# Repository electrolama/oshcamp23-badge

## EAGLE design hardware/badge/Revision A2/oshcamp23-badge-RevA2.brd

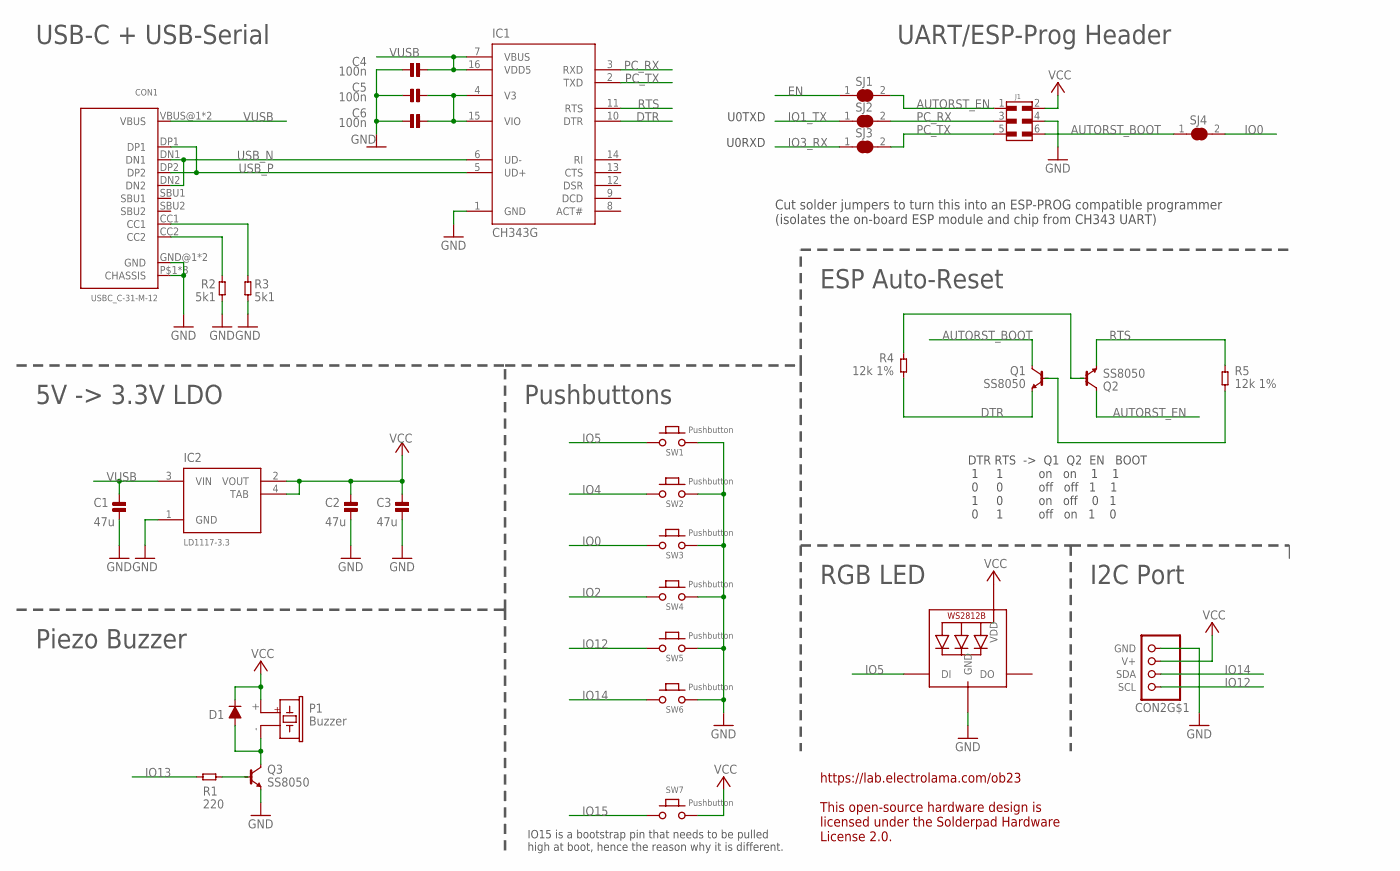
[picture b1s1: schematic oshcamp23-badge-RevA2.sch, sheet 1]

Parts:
C1, C2, C3: 47u; _PKG_C_1206; MPN CL31A476MPHNNNE; JLCASSY C96123
C4, C5, C6: 100n; _PKG_C_0402; JLCASSY C307331
CON1: USBC_C-31-M-12; JLCASSY C165948
CON2: STEMMA_I2C_QT; JST_SH4; JLCASSY C145956
D1: DIODE-SWITCHING-1N4148W; _PKG_SOD123
IC1: CH343G; _PKG_SOP16; JLCASSY C2844153
IC2: LD1117-3.3; _PKG_SOT223-4_TI-DCY4; JLCASSY C6186
J1: 61030621121; JLCASSY C780054
LED1: WS2812B5050; WS2812B
P1: Buzzer; MLT-8530; JLCASSY C94599
Q1, Q2, Q3: SS8050; SOT96P237X111-3N; JLCASSY C2150
R1: 220; _PKG_R_0603; JLCASSY C22962
R2, R3: 5k1; _PKG_R_0603; JLCASSY C23186
R4, R5: 12k 1%; _PKG_R_0402; JLCASSY C25752
SJ1, SJ2, SJ3, SJ4: SJ-SHORT
SW1, SW2, SW3, SW4, SW5, SW6, SW7: Pushbutton; GENERIC_SPNO_4P_6X6MM; JLCASSY C620316

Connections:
AUTORST_BOOT: J1.6, Q1.3 (C), SJ4.1
AUTORST_EN: J1.1, Q2.3 (C), SJ1.2
CH343_3V: C5.1, C6.1, IC1.4 (V3), IC1.15 (VIO)
DTR: IC1.10 (DTR), Q1.2 (E), R4.1
EN: SJ1.1; also elsewhere on the board
GND: C1.2, C2.2, C3.2, C4.2, C5.2, C6.2, CON1.GND@1 (GND), CON1.GND@2 (GND), CON1.P$1 (CHASSIS), CON1.P$2 (CHASSIS), CON1.P$3 (CHASSIS), CON1.P$4 (CHASSIS), CON1.P$5 (CHASSIS), CON1.P$6 (CHASSIS), CON1.P$7 (CHASSIS), CON1.P$8 (CHASSIS), CON2.1 (GND), IC1.1 (GND), IC2.1 (GND), J1.4, LED1.3-GND (GND), Q3.2 (E), R2.1, R3.1, SW1.P$3 (2), SW1.P$4 (2), SW2.P$3 (2), SW2.P$4 (2), SW3.P$3 (2), SW3.P$4 (2), SW4.P$3 (2), SW4.P$4 (2), SW5.P$3 (2), SW5.P$4 (2), SW6.P$3 (2), SW6.P$4 (2); also elsewhere on the board
IO0: SJ4.2, SW3.P$1 (1), SW3.P$2 (1); also elsewhere on the board
IO1_TX: SJ2.1; also elsewhere on the board
IO2: SW4.P$1 (1), SW4.P$2 (1); also elsewhere on the board
IO3_RX: SJ3.1; also elsewhere on the board
IO4: SW2.P$1 (1), SW2.P$2 (1); also elsewhere on the board
IO5: LED1.4-DIN (DI), SW1.P$1 (1), SW1.P$2 (1); also elsewhere on the board
IO12: CON2.4 (SCL), SW5.P$1 (1), SW5.P$2 (1); also elsewhere on the board
IO13: R1.2; also elsewhere on the board
IO14: CON2.3 (SDA), SW6.P$1 (1), SW6.P$2 (1); also elsewhere on the board
IO15: SW7.P$1 (1), SW7.P$2 (1); also elsewhere on the board
unnamed: Q1.1 (B), R5.1
unnamed: D1.2 (A), P1.-, Q3.3 (C)
unnamed: Q2.1 (B), R4.2
unnamed: CON1.CC1, R3.2
unnamed: CON1.CC2, R2.2
unnamed: Q3.1 (B), R1.1
PC_RX: IC1.3 (RXD), J1.3, SJ2.2
PC_TX: IC1.2 (TXD), J1.5, SJ3.2
RTS: IC1.11 (RTS), Q2.2 (E), R5.2
USB_N: CON1.DN1, CON1.DN2, IC1.6 (UD-)
USB_P: CON1.DP1, CON1.DP2, IC1.5 (UD+)
VCC: C2.1, C3.1, CON2.2 (V+), D1.1 (C), IC2.2 (VOUT), IC2.4 (TAB), J1.2, LED1.1-VDD (VDD), P1.+, SW7.P$3 (2), SW7.P$4 (2); also elsewhere on the board
VUSB: C1.1, C4.1, CON1.VBUS@1 (VBUS), CON1.VBUS@2 (VBUS), IC1.7 (VBUS), IC1.16 (VDD5), IC2.3 (VIN)

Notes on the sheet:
DTR RTS -> Q1 Q2 EN BOOT 1 1 on on 1 1 0 0 off off 1 1 1 0 on off 0 1 0 1 off on 1 0
U0TXD
U0RXD
Cut solder jumpers to turn this into an ESP-PROG compatible programmer (isolates the on-board ESP module and chip from CH343 UART)
USB-C + USB-Serial
UART/ESP-Prog Header
ESP Auto-Reset
RGB LED
I2C Port
Pushbuttons
5V -> 3.3V LDO
Piezo Buzzer
https://lab.electrolama.com/ob23 This open-source hardware design is licensed under the Solderpad Hardware License 2.0.
IO15 is a bootstrap pin that needs to be pulled high at boot, hence the reason why it is different.

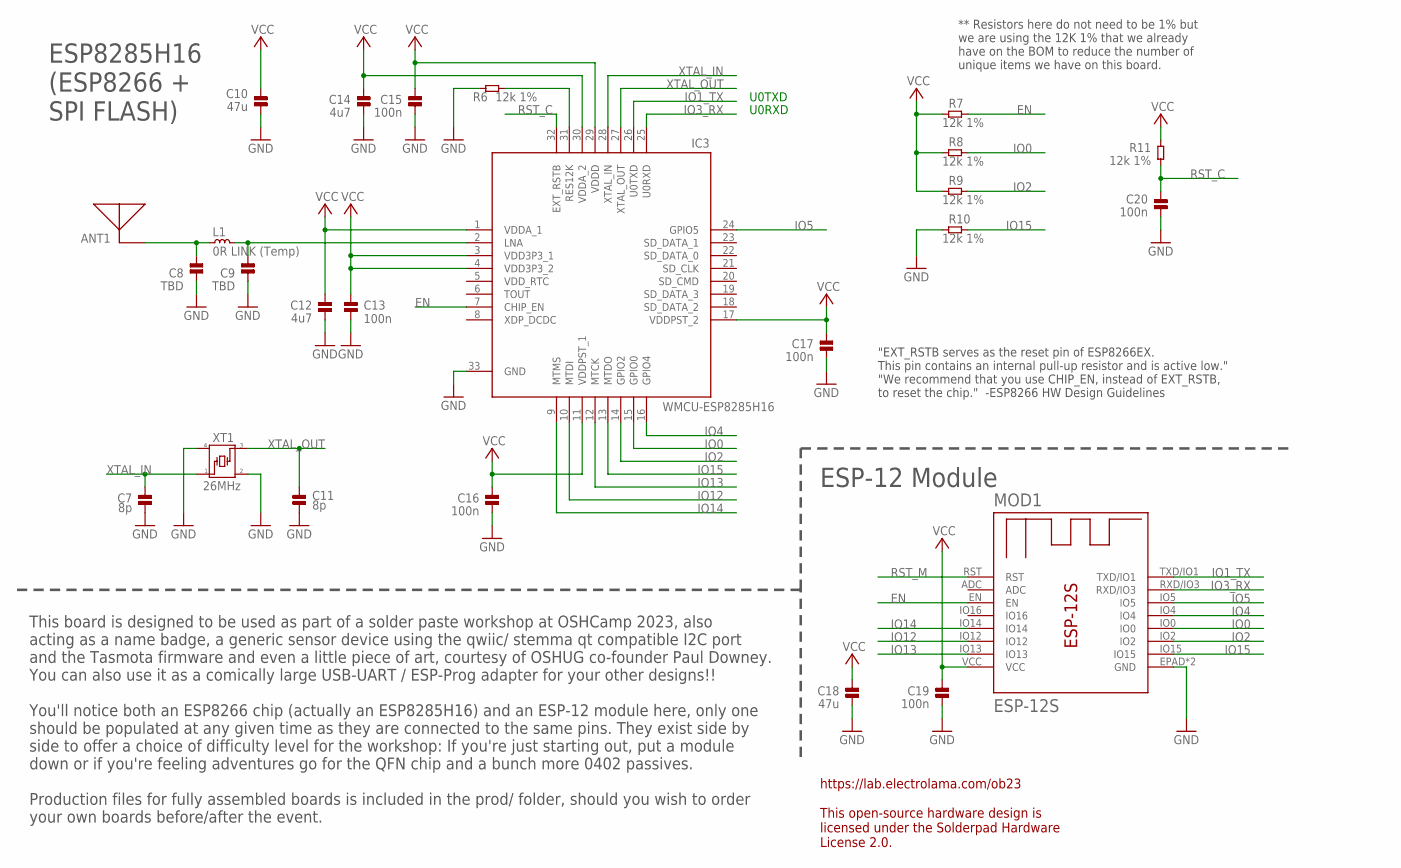
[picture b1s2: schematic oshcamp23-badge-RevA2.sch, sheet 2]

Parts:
ANT1: ANT3216LL00R2400A; YAGEO-ANT3216LL00R2400A; JLCASSY C293767
C7, C11: 8p; _PKG_C_0402; JLCASSY C1578
C8, C9: TBD; _PKG_C_0402_NOTHERMALS
C10, C18: 47u; _PKG_C_1206; MPN CL31A476MPHNNNE; JLCASSY C96123
C12, C14: 4u7; _PKG_C_0402_NOTHERMALS; JLCASSY C23733
C13, C15, C16, C17, C20: 100n; _PKG_C_0402_NOTHERMALS; JLCASSY C307331
C19: 100n; _PKG_C_0402; JLCASSY C307331
IC3: WMCU-ESP8285H16; QFN50P500X500X90-33N; JLCASSY C967019
L1: 0R LINK (Temp); _PKG_L_0402
MOD1: ESP-12S; JLCASSY C82898
R6, R7, R8, R9, R10, R11: 12k 1%; _PKG_R_0402; JLCASSY C25752
XT1: 26MHz; XTAL-4P-2016; JLCASSY C2762193

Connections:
ANT: C9.2, IC3.2 (LNA), L1.2
ANT': ANT1.S1, C8.2, L1.1
EN: IC3.7 (CHIP_EN), MOD1.EN, R7.2; also elsewhere on the board
GND: C7.1, C8.1, C9.1, C10.2, C11.1, C12.1, C13.1, C14.1, C15.1, C16.1, C17.1, C18.2, C19.2, C20.1, IC3.33 (GND), MOD1.EPAD (GND), MOD1.GND, R6.2, R10.1, XT1.2, XT1.4; also elsewhere on the board
IO0: IC3.15 (GPIO0), MOD1.IO0, R8.2; also elsewhere on the board
IO1_TX: IC3.26 (U0TXD), MOD1.TXD/IO1; also elsewhere on the board
IO2: IC3.14 (GPIO2), MOD1.IO2, R9.2; also elsewhere on the board
IO3_RX: IC3.25 (U0RXD), MOD1.RXD/IO3; also elsewhere on the board
IO4: IC3.16 (GPIO4), MOD1.IO4; also elsewhere on the board
IO5: IC3.24 (GPIO5), MOD1.IO5; also elsewhere on the board
IO12: IC3.10 (MTDI), MOD1.IO12; also elsewhere on the board
IO13: IC3.12 (MTCK), MOD1.IO13; also elsewhere on the board
IO14: IC3.9 (MTMS), MOD1.IO14; also elsewhere on the board
IO15: IC3.13 (MTDO), MOD1.IO15, R10.2; also elsewhere on the board
unnamed: IC3.31 (RES12K), R6.1
RST_C: C20.2, IC3.32 (EXT_RSTB), R11.1
RST_M: MOD1.RST
VCC: C10.1, C12.2, C13.2, C14.2, C15.2, C16.2, C17.2, C18.1, C19.1, IC3.1 (VDDA_1), IC3.3 (VDD3P3_1), IC3.4 (VDD3P3_2), IC3.11 (VDDPST_1), IC3.17 (VDDPST_2), IC3.29 (VDDD), IC3.30 (VDDA_2), MOD1.VCC, R7.1, R8.1, R9.1, R11.2; also elsewhere on the board
XTAL_IN: C7.2, IC3.28 (XTAL_IN), XT1.1
XTAL_OUT: C11.2, IC3.27 (XTAL_OUT), XT1.3

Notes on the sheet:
U0TXD
U0RXD
"EXT_RSTB serves as the reset pin of ESP8266EX. This pin contains an internal pull-up resistor and is active low." "We recommend that you use CHIP_EN, instead of EXT_RSTB, to reset the chip." -ESP8266 HW Design Guidelines
This board is designed to be used as part of a solder paste workshop at OSHCamp 2023, also acting as a name badge, a generic sensor device using the qwiic/ stemma qt compatible I2C port and the Tasmota firmware and even a little piece of art, courtesy of OSHUG co-founder Paul Downey. You can also u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
https://lab.electrolama.com/ob23 This open-source hardware design is licensed under the Solderpad Hardware License 2.0.
ESP-12 Module
ESP8285H16 (ESP8266 + SPI FLASH)
ANT1
** Resistors here do not need to be 1% but we are using the 12K 1% that we already have on the BOM to reduce the number of unique items we have on this board.

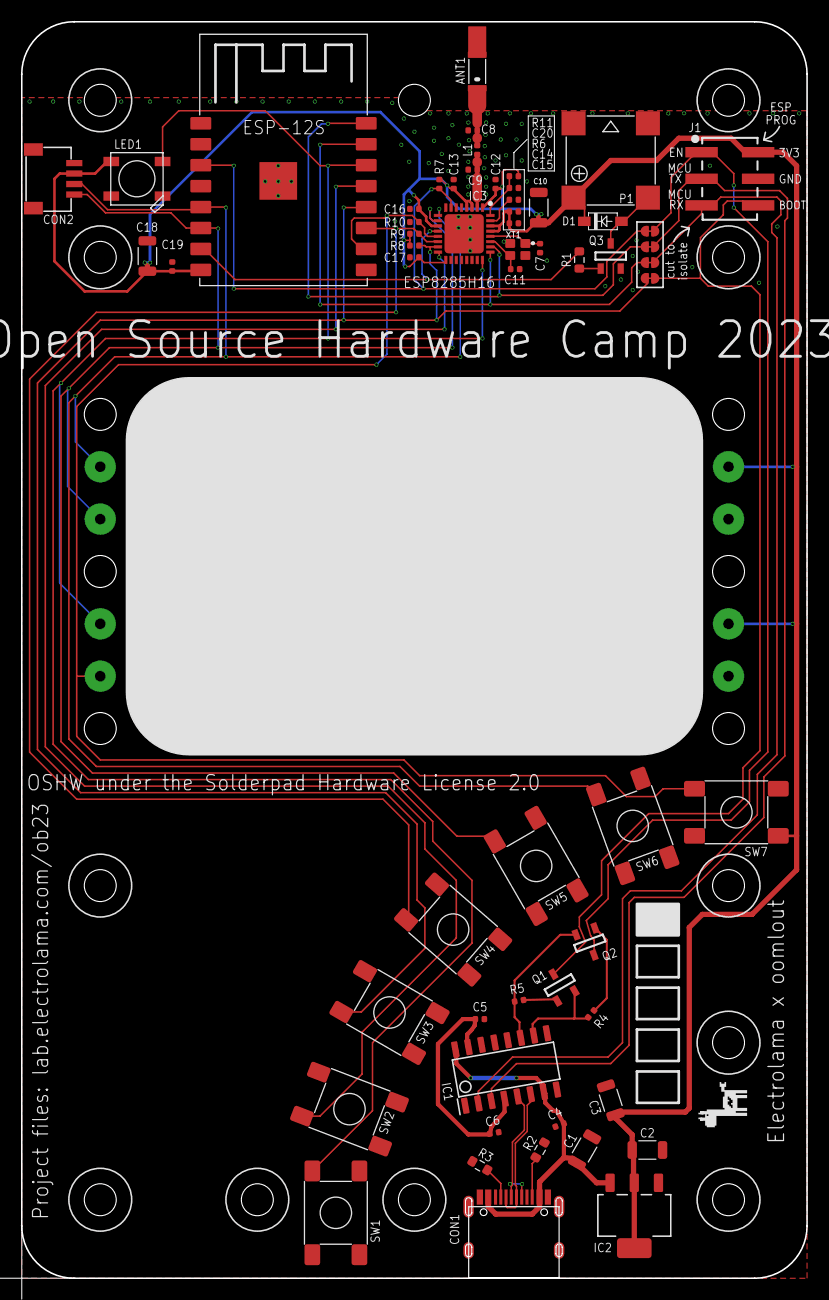
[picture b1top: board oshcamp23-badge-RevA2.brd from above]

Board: 2 copper layers, 75.0 x 120.0 mm, 58 parts (0 on the bottom side), 35 nets.

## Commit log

2023-08-06 add LICENSE and ignores
2023-08-06 initial commit for badge RevA2 EAGLE files and schematic PDF
2023-08-06 add refs
2023-08-06 add production files for badge RevA2
2023-08-06 add topper RevA1
2023-08-06 initial commit for Arduino hardware test fw
2023-08-06 added decorations and images
2023-08-07 added oomp generations
2023-08-07 added mechanical generations
2023-08-07 mechanical drawing
2023-08-07 better oomp gens and fixed adapter.
2023-08-07 removed silly dxf issues
2023-08-08 added oomp_yaml
2023-08-08 fixed oomp.yaml
2023-08-23 placeholder for docs
2023-08-26 add iboms for both kit variants
2023-08-26 initial commit for pages enabled branch
2023-08-26 update index
2023-08-26 add a bit of style
2023-08-26 add pcb pngs
2023-08-26 add more links
2023-08-26 update pcb front higher res now
2023-08-26 link to pages

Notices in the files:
hardware/badge/Revision A2/oshcamp23-badge-RevA2.brd:
OSHW under the Solderpad Hardware License 2.0
parts and their libraries:
microbuilder: This work is placed in the public domain, and may be freely used for commercial and non-commercial work with the following conditions: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
Wurth_Connectors_WR-PHD: Copyright: Würth Elektronik
